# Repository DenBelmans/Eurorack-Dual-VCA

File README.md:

# Eurorack-Dual-VCA
An 8hp dual VCA module for Eurorack. Based on Electricdruids 'Vintage VCA'. You can learn everything about the schematic on their blog: https://electricdruid.net/design-a-eurorack-vintage-vca-with-the-lm13700/

This is my first Eurorack module, I hope there are many more to come!
If you try this out, feel free to contact me with questions, critique, or send me some pictures of the finished product!

If there are any issues with any of the files, please contact me. I made this before I knew I would be sharing everything online.

***** BUILD INSTRUCTIONS *****

To make your lifes easier I have updated the silkscreen to include the component values.
While soldering the headers, I recommend you stack the pcb's with the unsoldered headers mated in between. Then fix the PCBs together with the standoffs and screws to keep things together. Then solder the connectors.
When installing the front panel, make sure the text on the panel is oriented in the same direction as the text on the PCBs. Otherwise things will not work as expected. In future designs I will try to make the panel non-symmetrical.

***** HISTORY *****

31/12/2020: First tests showed some issues with the design which were solved before uploading the files to GitHub, though the current files are not tested yet, this will likely happen later this month when I place a new order for PCBs.

20/01/2021: I have changed a few small things and will be ordering the current PCB design in the next week. I will update this description once I have tested it and confirmed that everything works as intended, no reversed pots or switched jacks :)

07/02/2021: As of today everything in this repository is finalized and tested. Feel free to place orders for PCBs with the provided gerbers or make changes using the KiCAD files!

07/03/2021: I updated the gerbers and kicad files again. Now the component values will be printed on the PCBs in silkscreen for easier assembly!

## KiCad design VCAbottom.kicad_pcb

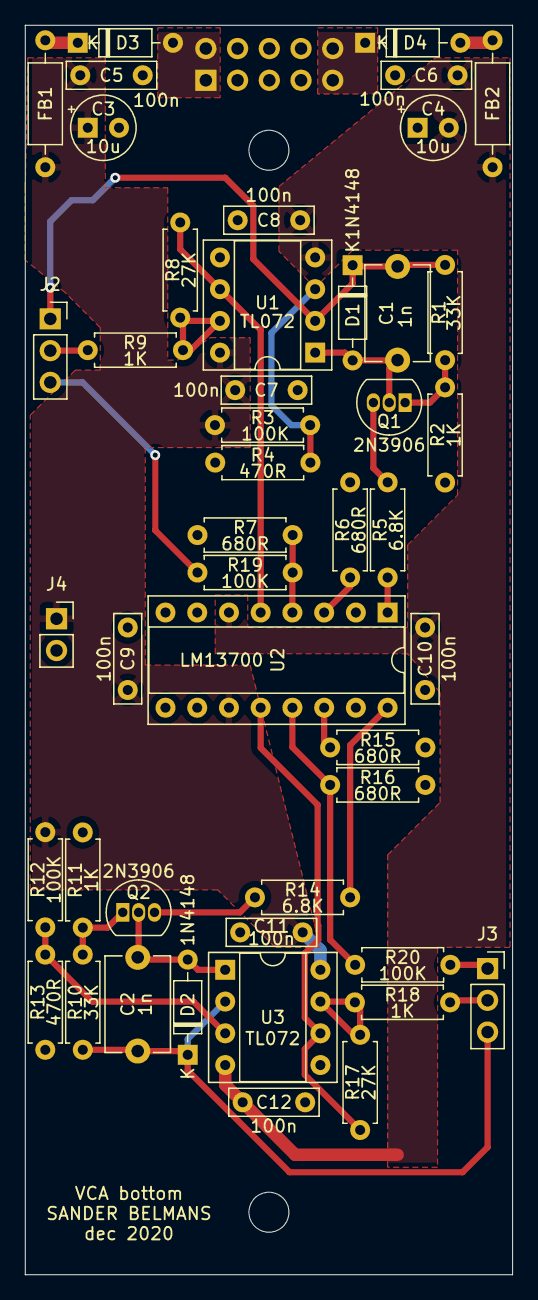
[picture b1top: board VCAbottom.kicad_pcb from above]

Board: 2 copper layers, 39.0 x 100.0 mm, 49 parts (1 on the bottom side), 31 nets.

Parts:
C1, C2: 1n; C_Disc_D7.5mm_W5.0mm_P7.50mm
C3, C4: 10u; CP_Radial_Tantal_D5.0mm_P2.50mm
C5, C6, C7, C8, C9, C10, C11, C12: 100n; C_Rect_L7.0mm_W2.0mm_P5.00mm
D1, D2, D3, D4: 1N4148; D_DO-35_SOD27_P7.62mm_Horizontal
FB1, FB2: Ferrite_Bead; R_Axial_DIN0207_L6.3mm_D2.5mm_P10.16mm_Horizontal
H1, H2: MountingHole; MountingHole_3.2mm_M3
J1: PWR; PinSocket_2x05_P2.54mm_Vertical
J2: sigA; PinSocket_1x03_P2.54mm_Vertical
J3: sigB; PinSocket_1x03_P2.54mm_Vertical
J4: PWR2; PinSocket_1x02_P2.54mm_Vertical
Q1, Q2: 2N3906; TO-92_Inline
R1, R10: 33K; R_Axial_DIN0207_L6.3mm_D2.5mm_P7.62mm_Horizontal
R2, R9, R11, R18: 1K; R_Axial_DIN0207_L6.3mm_D2.5mm_P7.62mm_Horizontal
R3, R12, R19, R20: 100K; R_Axial_DIN0207_L6.3mm_D2.5mm_P7.62mm_Horizontal
R4, R13: 470R; R_Axial_DIN0207_L6.3mm_D2.5mm_P7.62mm_Horizontal
R5, R14: 6.8K; R_Axial_DIN0207_L6.3mm_D2.5mm_P7.62mm_Horizontal
R6, R7, R15, R16: 680R; R_Axial_DIN0207_L6.3mm_D2.5mm_P7.62mm_Horizontal
R8, R17: 27K; R_Axial_DIN0207_L6.3mm_D2.5mm_P7.62mm_Horizontal
U1, U3: TL072; DIP-8_W7.62mm_Socket
U2: LM13700; DIP-16_W7.62mm_Socket

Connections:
+12V: C3.1, C5.2, C7.2, C9.2, C11.2, FB1.2, J4.1, R3.2, R12.2, U1.8, U2.11, U3.8
-12V: C4.2, C6.1, C8.1, C10.1, C12.1, FB2.2, U1.4, U2.6, U3.4
/CVA: C1.2, D1.1, J2.1, R1.2, U1.2
/CVB: C2.2, D2.1, J3.3, R10.2, U3.2
/SignalInA: J2.3, R19.2
/SignalInB: J3.1, R20.2
/SignalOutA: J2.2, R9.1
/SignalOutB: J3.2, R18.1
GND: C3.2, C4.1, C5.1, C6.2, C7.1, C8.2, C9.1, C10.2, C11.1, C12.2, J1.3, J1.4, J1.5, J1.6, J1.7, J1.8, J4.2, R2.1, R4.1, R6.2, R7.2, R11.1, R13.1, R15.2, R16.2, U1.5, U3.5
unnamed: C1.1, D1.2, Q1.2, U1.1
unnamed: C2.1, D2.2, Q2.2, U3.1
unnamed: D3.1, FB1.1
unnamed: D3.2, J1.1, J1.2
unnamed: D4.1, J1.9, J1.10
unnamed: D4.2, FB2.1
unnamed: Q1.1, R1.1, R2.2
unnamed: Q1.3, R5.2
unnamed: Q2.1, R10.1, R11.2
unnamed: Q2.3, R14.2
unnamed: R3.1, R4.2, U1.3
unnamed: R5.1, U2.1
unnamed: R6.1, U2.3
unnamed: R8.1, R9.2, U1.7
unnamed: R8.2, U1.6, U2.5
unnamed: R12.1, R13.2, U3.3
unnamed: R14.1, U2.16
unnamed: R15.1, U2.14
unnamed: R16.1, R20.1, U2.13
unnamed: R17.1, R18.2, U3.7
unnamed: R17.2, U2.12, U3.6
unnamed: R7.1, R19.1, U2.4

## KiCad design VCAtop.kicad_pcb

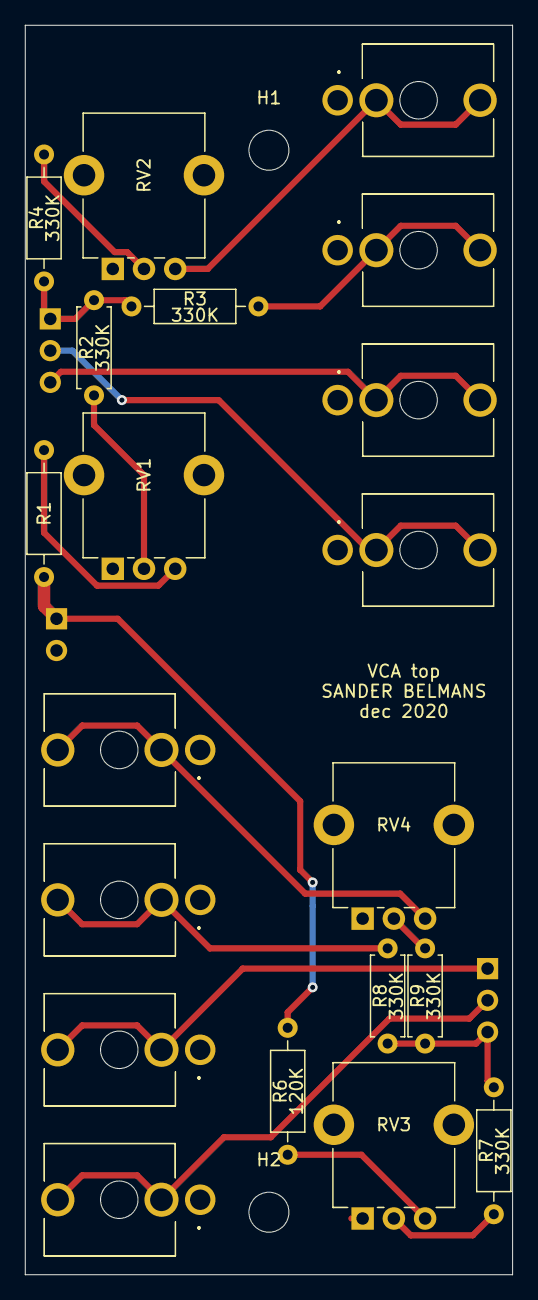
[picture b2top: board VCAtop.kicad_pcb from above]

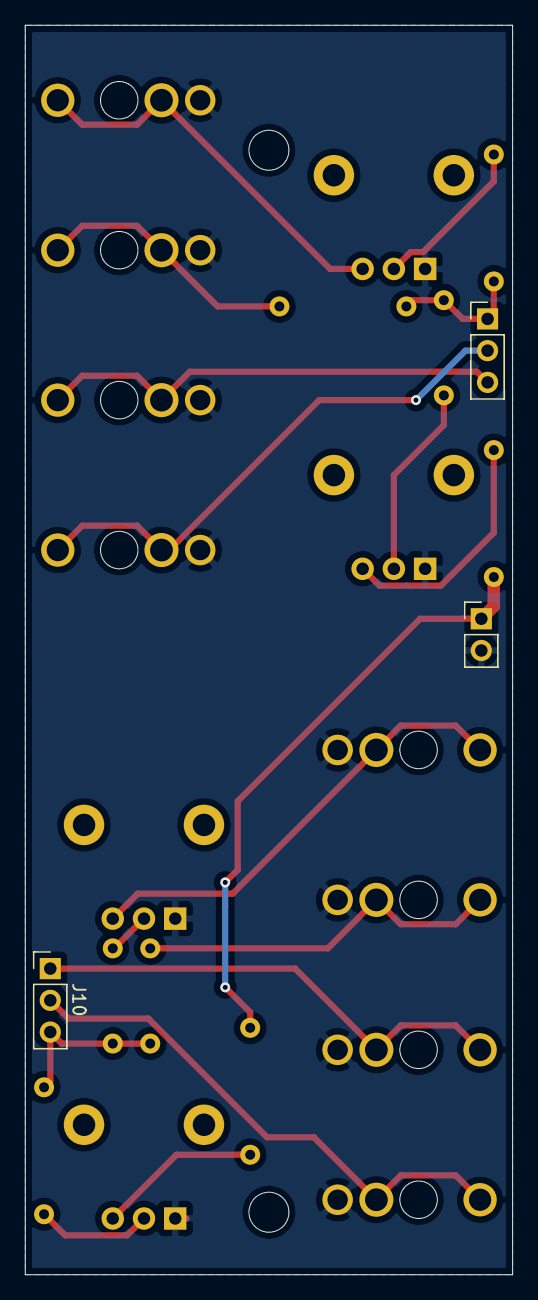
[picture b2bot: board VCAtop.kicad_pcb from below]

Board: 2 copper layers, 39.0 x 100.0 mm, 25 parts (3 on the bottom side), 18 nets.

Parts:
H1, H2: MountingHole; MountingHole_3.2mm_M3
J1: EnvelopeA; Thonkiconn
J2: CVA; Thonkiconn
J3: SignalInA; Thonkiconn
J4: SignalOutA; Thonkiconn
J5, J10: Conn_01x03_Male; PinHeader_1x03_P2.54mm_Vertical
J6: CVB; Thonkiconn
J7: EnvB; Thonkiconn
J8: SignalInB; Thonkiconn
J9: SignalOutB; Thonkiconn
J11: PWR; PinHeader_1x02_P2.54mm_Vertical
R1, R6: 120K; R_Axial_DIN0207_L6.3mm_D2.5mm_P10.16mm_Horizontal
R2, R8, R9: 330K; R_Axial_DIN0207_L6.3mm_D2.5mm_P7.62mm_Horizontal
R3, R4, R7: 330K; R_Axial_DIN0207_L6.3mm_D2.5mm_P10.16mm_Horizontal
RV1: BiasA; Potentiometer_Alpha_RD901F-40-00D_Single_Vertical_CircularH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
RV2: CV_amtA; Potentiometer_Alpha_RD901F-40-00D_Single_Vertical_CircularH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
RV3: BiasB; Potentiometer_Alpha_RD901F-40-00D_Single_Vertical_CircularH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
RV4: CV_amtB; Potentiometer_Alpha_RD901F-40-00D_Single_Vertical_CircularH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

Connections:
+12V: J11.1, R1.2, R6.2
/CVA: J5.1, R2.1, R3.1, R4.1
/CVB: J10.3, R7.1, R8.1, R9.1
/SignalInA: J3.R, J3.T, J5.3
/SignalInB: J8.R, J8.T, J10.1
/SignalOutA: J4.R, J4.T, J5.2
/SignalOutB: J9.R, J9.T, J10.2
GND: J1.S, J2.S, J3.S, J4.S, J6.S, J7.S, J8.S, J9.S, J11.2, RV1.1, RV2.1, RV3.1, RV4.1
unnamed: J1.R, J1.T, R3.2
unnamed: J2.R, J2.T, RV2.3
unnamed: J6.R, J6.T, RV4.3
unnamed: J7.R, J7.T, R8.2
unnamed: R1.1, RV1.3
unnamed: R2.2, RV1.2
unnamed: R4.2, RV2.2
unnamed: R6.1, RV3.3
unnamed: R7.2, RV3.2
unnamed: R9.2, RV4.2
